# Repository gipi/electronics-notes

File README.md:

Repository containing my notes about electronics.

You can read it at [Read the docs](http://electronics-notes.readthedocs.org/).

## Getting started

You need to install the dependencies

```
$ python3 -m pip install --user mkdocs python-markdown-math
```

and to read locally you need to do a simple

```
$ mkdocs serve
```

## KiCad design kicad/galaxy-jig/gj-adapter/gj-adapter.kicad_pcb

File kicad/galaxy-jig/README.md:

# Galaxy JIG

This is a board to easily develop on Samsung's smartphones that have the serial
port activated using a particular resistor value between the ``ID`` and ``GND``
of the ``USB`` connection.

To multiplex between the two possible routes I'm using the
[ADG723](https://www.analog.com/media/en/technical-documentation/data-sheets/adg721_722_723.pdf),
a STSP switch. and the ``mode`` signal as input for the mux.

## Soldering procedure

 1. solder the ``ADG723``
 2. check they are working correctly
 3. solder the ``USB`` connector
 4. build the micro ``USB`` cable and use it to check connectivity of the connector
 5. solder the ``USB`` cable
 6. solder the ``UART`` header
 7. solder the 619k resistor

## TODO

 - **rethink the switching interface**, probably I should use the [TS3USB221](https://www.ti.com/lit/ds/symlink/ts3usb221.pdf)
 - add also a variable resistor so to change the value easily
 - move test point to the ``UART HEADER`` so to expose ``VCC`` more easily
 - add labels indicating the signal passing through the switches
 - modify footprint ``USB`` micro connector to allow easier hand soldering
 - add two leds to indicate the mode
 - use a ``FTDI`` chip to directly talk serial over ``USB``

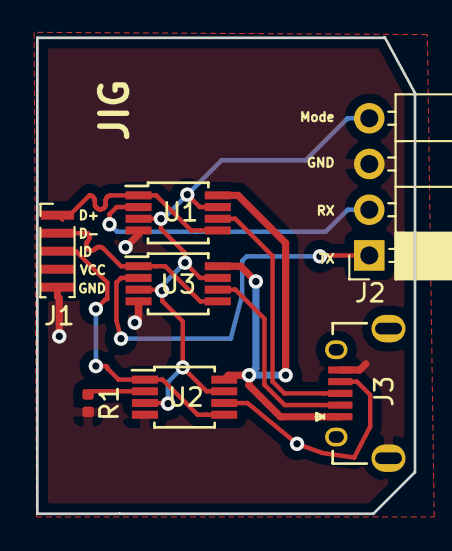
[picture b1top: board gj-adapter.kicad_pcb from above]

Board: 2 copper layers, 21.0 x 26.5 mm, 7 parts (0 on the bottom side), 12 nets.

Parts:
J1: Conn_01x05; PinHeader_1x05_P1.00mm_Vertical
J2: Conn_01x04; PinSocket_1x04_P2.54mm_Horizontal
J3: USB_B_Micro; ZX62D-B-5PA8
R1: 619k; R_0402_1005Metric
U1, U2, U3: ADG723; MSOP-8_3x3mm_P0.65mm

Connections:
D+: J1.1, U1.1, U1.5
D+-PC: J3.3, U1.6
D-: J1.2, U3.1, U3.5
D--PC: J3.2, U3.6
GND: J1.5, J2.3, J3.5, J3.6, R1.2, U1.4, U2.4, U3.4
ID-PC: J3.4, U2.6
ID-device: J1.3, U2.1, U2.5
Mode: J2.4, U1.3, U1.7, U2.3, U2.7, U3.3, U3.7
unnamed: R1.1, U2.2
RX: J2.2, U1.2
TX: J2.1, U3.2
VCC: J3.1, U1.8, U2.8, U3.8

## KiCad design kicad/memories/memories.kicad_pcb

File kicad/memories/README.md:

# Memories

Here I'm trying to create a header for the Mojo development board that allows
to have the basic minimal peripherals for a running system:

 - Flash
 - SDRAM
 - VGA
 - PS2

In this directory there are the KiCAD files and this is the hand soldered version 1.0

## Flash

The flash memory under experimentation is the NAND512W3A2C, with 512 Mbit and x8 of bus width.

 - [Datasheet](https://4donline.ihs.com/images/VipMasterIC/IC/SGST/SGSTS20436/SGSTS20436-1.pdf)

## SRAM

The SDRAM used here is the MT48LC32M8A2.

 - [Datasheet](256Mb_sdr.pdf)
 - [Tutorial](https://embeddedmicro.com/blogs/tutorials/sdram-verilog) about writing a SDRAM controller in Verilog

## VGA

It's a VGA with 3 bits for color channel using a resistor ladder.

## Todo

 - UART
 - SPI
 - I2C
 - LCD controller
 - SDCard

probably are needed only as explicit routed pinout.

## Design errors

 - The pad of the ``AMS1117`` is the ``vout`` not ground (Fixed)
 - enlarge the pad so to make it more hand-solderable
 - add mask to the Open Hardware logo (fixed)
 - reverse voltage protection
 - overvoltage protection
 - enlarge holes for VGA and PS/2 (fixed)
 - fix R-2R ladder

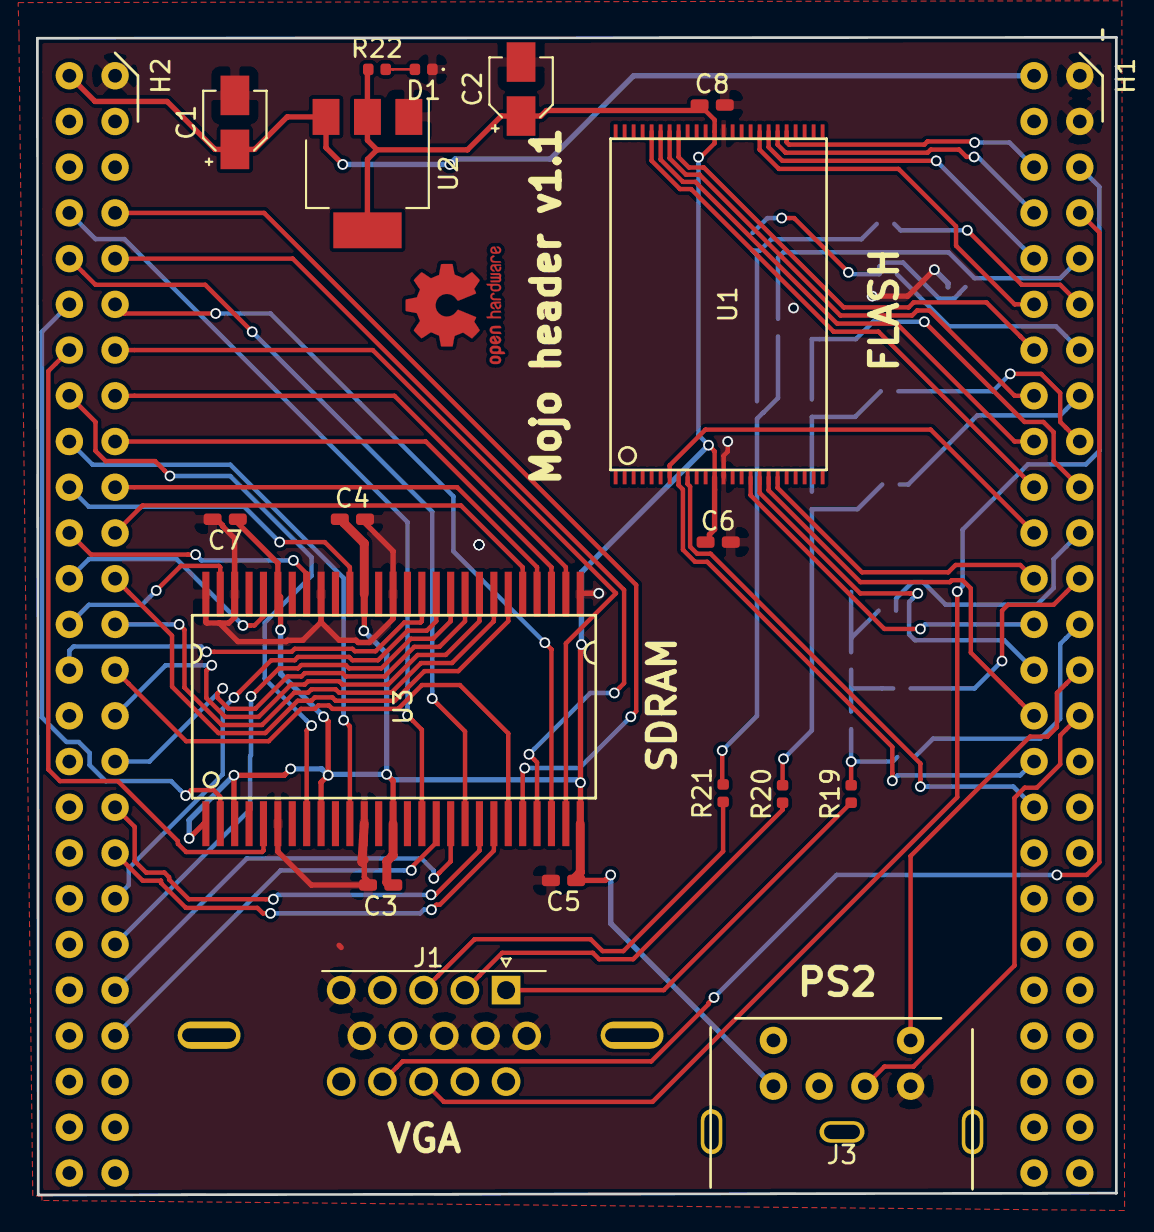
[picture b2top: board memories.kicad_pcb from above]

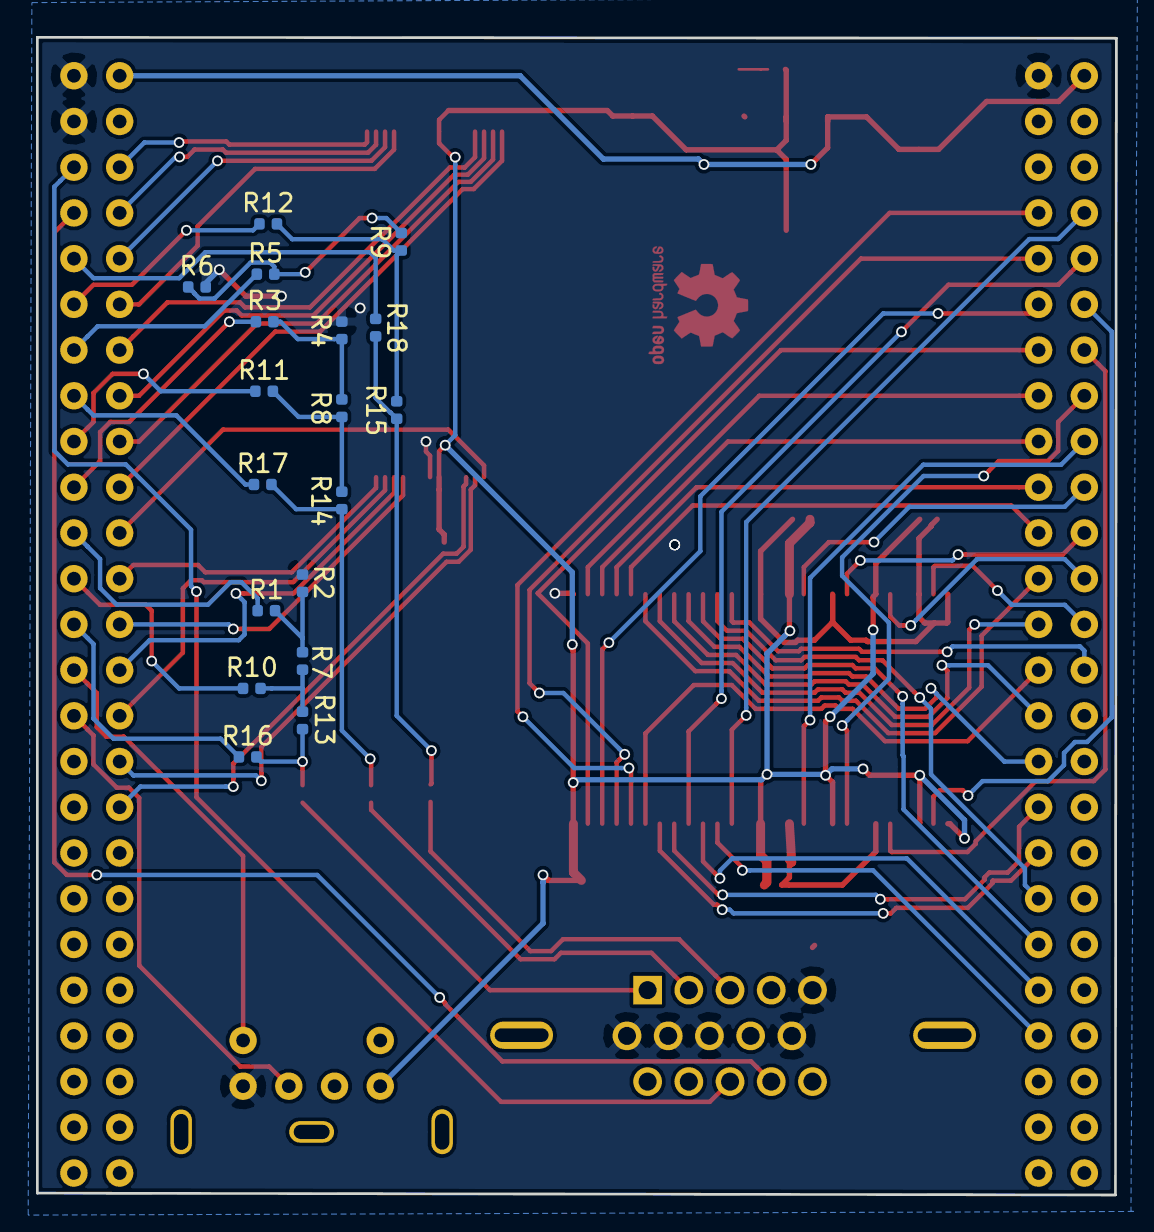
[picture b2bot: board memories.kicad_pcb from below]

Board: 2 copper layers, 59.9 x 64.3 mm, 38 parts (18 on the bottom side), 74 nets.

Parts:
C1, C2: CP1; CP_Elec_3x5.3
C3, C4, C5, C6, C7, C8: C; C_0402_handSoldering
D1: LED; LED_0402_1005Metric
H1: Header; mojo_header
H2: mojo_header_lower; mojo_header
J1: DB15_Female_HighDensity; DSUB-15-HD_Female
J3: DIN-6; mini-DIN6
R1, R2, R3, R4, R5, R6, R10, R11, R12, R16, R17, R18: 560; R_0402_1005Metric
R7, R8, R9, R13, R14, R15: 270; R_0402_1005Metric
R19, R20, R21: 0; R_0402_1005Metric
R22: R; R_0402_1005Metric
U1: NAND512
U2: AMS1117-3V3; SOT-223
U3: MT48LC32M8A2; TSOP_54

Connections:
3V3: C2.1, C3.1, C4.1, C5.1, C6.1, C7.1, C8.1, J3.4, R22.1, U1.12, U1.37, U2.2, U2.4, U3.1, U3.3, U3.9, U3.14, U3.27, U3.43, U3.49
/DQ0: H2.31, U3.2
/DQ1: H2.32, U3.5
/DQ2: H2.33, U3.8
/DQ3: H2.34, U3.11
/DQ4: H2.35, U3.44
/DQ5: H2.36, U3.47
/DQ6: H2.37, U3.50
/DQ7: H2.38, U3.53
/VGA/VGA_B0: H1.5, R18.1
/VGA/VGA_B1: H1.6, R12.1
/VGA/VGA_B2: H1.7, R5.1
/VGA/VGA_B_OUT: J1.3, R21.1
/VGA/VGA_G0: H1.8, R17.1
/VGA/VGA_G1: H1.9, R11.1
/VGA/VGA_G2: H1.10, R3.1
/VGA/VGA_G_OUT: J1.2, R20.1
/VGA/VGA_HSYNC: H1.3, J1.13
/VGA/VGA_R0: H1.13, R16.1
/VGA/VGA_R1: H1.12, R10.1
/VGA/VGA_R2: H1.11, R1.1
/VGA/VGA_R_OUT: J1.1, R19.1
/VGA/VGA_VSYNC: H1.4, J1.14
DQM: H2.39, U3.39
GND: C1.2, C2.2, C3.2, C4.2, C5.2, C6.2, C7.2, C8.2, D1.1, H1.1, H1.2, H2.1, J1.5, J1.6, J1.7, J1.8, J1.10, J3.3, R2.2, R4.2, R6.2, U1.13, U1.36, U2.1, U3.6, U3.12, U3.28, U3.41, U3.46, U3.52, U3.54
unnamed: D1.2, R22.2
unnamed: H1.28, U1.29
unnamed: H1.29, U1.30
unnamed: H1.30, U1.31
unnamed: H1.31, U1.32
unnamed: H1.32, U1.41
unnamed: H1.33, U1.42
unnamed: H1.34, U1.43
unnamed: H1.35, U1.44
unnamed: H1.36, U1.7
unnamed: H1.37, U1.19
unnamed: H1.38, U1.16
unnamed: H1.39, U1.17
unnamed: H1.40, U1.18
unnamed: H1.41, U1.8
unnamed: H1.42, U1.9
unnamed: H2.4, U3.23
unnamed: H2.5, U3.24
unnamed: H2.6, U3.25
unnamed: H2.7, U3.26
unnamed: H2.8, U3.29
unnamed: H2.9, U3.30
unnamed: H2.10, U3.31
unnamed: H2.11, U3.32
unnamed: H2.12, U3.33
unnamed: H2.13, U3.34
unnamed: H2.14, U3.22
unnamed: H2.15, U3.35
unnamed: H2.16, U3.36
unnamed: H2.17, U3.20
unnamed: H2.18, U3.21
unnamed: H2.19, U3.38
unnamed: H2.20, U3.37
unnamed: H2.21, U3.18
unnamed: H2.22, U3.17
unnamed: H2.29, U3.16
unnamed: H2.30, U3.19
unnamed: R1.2, R2.1, R7.2
unnamed: R3.2, R4.1, R8.2
unnamed: R5.2, R6.1, R9.2
unnamed: R7.1, R10.2, R13.2
unnamed: R8.1, R11.2, R14.2
unnamed: R9.1, R12.2, R15.2
unnamed: R13.1, R16.2, R19.2
unnamed: R14.1, R17.2, R20.2
unnamed: R15.1, R18.2, R21.2
PS2_CLK: H1.14, J3.5
PS2_DATA: H1.15, J3.1
V_EXTERNAL: C1.1, H1.26, H2.26, U2.3

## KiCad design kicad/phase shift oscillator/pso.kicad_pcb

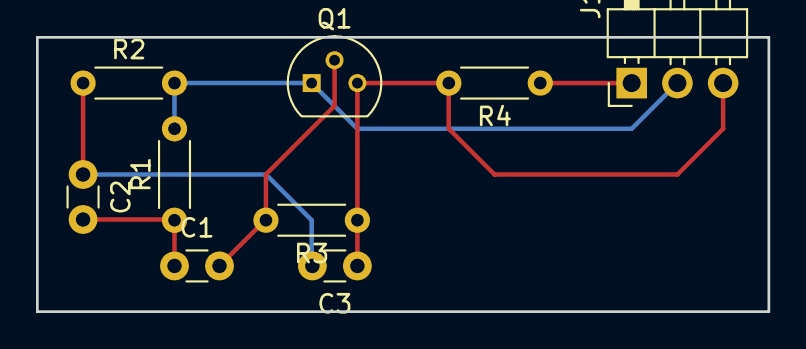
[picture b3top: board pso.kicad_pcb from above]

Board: 2 copper layers, 40.6 x 15.2 mm, 9 parts (0 on the bottom side), 6 nets.

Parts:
C1, C2, C3: 10nF; C_Disc_D3.0mm_W1.6mm_P2.50mm
J1: Conn_01x03; Pin_Header_Angled_1x03_Pitch2.54mm
Q1: 2N3904; TO-92_Molded_Narrow
R1, R2, R4: 2.2k; R_Axial_DIN0204_L3.6mm_D1.6mm_P5.08mm_Horizontal
R3: 220k; R_Axial_DIN0204_L3.6mm_D1.6mm_P5.08mm_Horizontal

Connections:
GND: J1.2, Q1.1, R1.2, R2.2
unnamed: C1.1, C2.2, R1.1
unnamed: C1.2, Q1.2, R3.2
unnamed: C2.1, C3.2, R2.1
VCC: J1.1, R4.1
Vout: C3.1, J1.3, Q1.3, R3.1, R4.2

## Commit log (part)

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2016-10-25 Add piece of code.
2016-10-26 fpga: counter increase with button pressing.
2016-12-02 Add links.
2016-12-13 Add note.
2016-12-30 Add Kicad links.
2017-01-10 Improve logic level notes.
2017-02-05 Improve KiCAD.
2017-02-05 Add an EasyDriver example sketch.
2017-02-12 Add opamp section.
2017-02-12 Add TODO.
2017-02-18 Add section about tape.
2017-02-18 Add note about enameled wire.
2017-02-20 Add 3D section.
2017-02-27 Add note about FDM.
2017-03-08 Add video.
2017-03-26 Try to use coregen.
2017-04-23 kicad: add simple audio amplifier circuit.
2017-05-08 Add Atmel's datasheets section.
2017-05-08 Add note about datasheet related infos.
2017-05-08 Fix link.
2017-05-15 Add example for setting fuse with avrdude.
2017-05-16 fpga: first module to dirty-glitching.
2017-05-19 fpga: very dirty code to glitch a clock.
2017-05-29 Fix.
2017-06-06 avr: add ISP pinout.
2017-06-06 laws: add note.
2017-06-06 RN42: improve info about default conf connection.
2017-06-07 RN42: add link to firmware stuff.
2017-06-30 RN42: update BOM.
2017-08-09 add SMA connectors information.
2017-12-06 VGA: add schematics.
2017-12-06 Add AVR444 application note code ported to avr-gcc.
2017-12-10 Add phase oscillator with kicad.
2017-12-10 Add page about simulation with spice.
2017-12-16 Dump some links.
2018-01-10 fpga: add PS2 simple controller.
    No error detection!
2018-01-10 fpga: add shift register verilog implementation.
2018-01-11 fpga/VGAGlyph: big rework.
2018-01-12 fpga/VGA: fix constraints file.
2018-01-12 fpga/VGAGlyph: fix reversed glyphs ROM and glyph_address.
2018-01-13 fpga/VGAGLyph: fix font rendering.
2018-01-13 fpga/VGAGlyph: add testbench for the framebuffer module.
    This testbench is probably bad written.
2018-02-19 Add script to read data from the SIGLENT SDS1102CML oscilloscope.
2018-02-20 test_visa: close device once.
2018-02-20 test_visa: display IDN for all the command involving the opened device.
2018-02-20 test_visa: add dumpscreen command.
2018-02-20 test_visa: add waveform dumping command.
2018-03-17 fpga: project GlitchGen.
2018-03-22 fpga/mojo/GlitchGen: add Arduino sketch.
2018-03-22 fpga/mojo/GlitchGen: refactor module for clock generation.
2018-04-11 GlitchGen: single stepping OK!
2018-04-11 GlitchGen: fix typo.
2018-04-11 GlitchGen: remove internal useless signal.
2018-04-11 GlitchGen: put the mojo clock into the clock network.
    In this way we can use it as a clock in the following modules.
2018-04-11 GlitchGen: make leds indicate some useful state.
2018-05-07 ESC: add simple code to use an ESC with arduino.
2018-05-10 PS/2: add working code.
2018-06-14 VGAGlyph: fix synch issue (?).
2018-06-14 VGAGlyph: use the same clock for h/vsync and framebuffer.
2018-06-14 Add reset input to VGA module.
2018-06-16 Change default net type to none.
2018-06-16 Let inDisplayArea be in sync with CounterX and CounterY.
2018-06-16 Delay also inDisplayArea.
2018-06-16 Improve comment.
2018-07-16 kicad: add mojo shield.
    It contains SDRAM, Flash, VGA and PS2.
2018-08-19 Fix AMS1117 pad net.
    In the original datasheet is not indicated that the bigger pad is vout
    and not ground how any sensible human could think.
2018-08-27 Fix the read the docs configuration file.
2018-09-08 fpga: fix UCF for SDRAM.
2018-09-08 fpga: rename variable.
2018-09-08 kicad: improve info about memories board.
2018-09-12 kicad: mojo header PS/2 holes enlargement.
2018-09-13 kicad: enlarged footprint for capacitor 0402 for hand soldering.
2018-09-24 kicad: fix name for mojo header pins.
2018-09-24 kicad/memories/pcb: fix R-2R ladder labels.
2018-10-03 fpga/VGA: upgrade controller to use 9-bit color depth.
2018-12-04 AVR/KeyboardMatrixRecovery: add POC.
2018-12-07 KeyboardMatrixRecovery: improve matrix recovery sketch.
    Now print only a key the moment when is pressed and output a binary packet.
2018-12-08 RN42: add datasheet.
2018-12-09 AVR/KeyboardMatrixRecovery: update README.
2018-12-28 Fix markdown extension error.
    <Config value: 'markdown_extensions'. Error: Failed to initiate extension 'math': 'module' object has no attribute 'makeExtension'>
    probably the naming convention is changed and had to be fixed, see
    <https://python-markdown.github.io/change_log/release-2.5/>.
2019-02-03 VGASOC: add ring_counter module and verilator POC.
2019-03-31 kicad: add samsung-jig.
2019-03-31 kicad: semi-final version of galaxy-jig.
2019-04-07 Add diagram of the JTAG stack.
2019-04-07 Fix typo.
2019-05-19 kicad/galaxy-jig: add notes.
2020-05-12 fpga/VGAGlyph: implement block ram and its simulation.
2020-05-12 fgpa/VGAGlyph: reimplement block rom for the glyph with simulation.
    Launch sim/obj_dir/Vglyph_rom and see the output of the block rom.
2020-05-12 fpga: add reset signal to hvsync_generator.
2020-05-12 fpga/VGAGlyph: rework verilog so to have simulation.
    $ cd fpga/mojo/VGAGlyph/sim
    $ make vga && ./obj_dir/VVGA
    ...
    [+] starting VGA simulation
    [-> dumping frame frames/frame-00000000.bmp at idx 6]
    [-> dumping frame frames/frame-00000001.bmp at idx 1182312]
2020-05-14 fpga/VGASOC: start implementing CPU.
2020-05-17 fpga/VGASOC: first implementation of the load instruction assembly.
2020-05-17 Add some links and notes.
2020-05-17 fpga/VGAGlyph: add clean target.
2020-05-17 fpga/VGASOC: add note about flags.
2020-05-17 fpga/VGASOC: fix compilation warning.
2020-05-18 fpga/VGASOC: remove MOVE instruction.
    Can be implemented with "ld rd, rs".
2020-05-21 fpga/VGASOC: factorize code about pipeline and add tests.
2020-05-21 Fix bug on parsing left operand.
2020-05-21 fpga/VGASOC: rework a little LOAD instruction assembly.
2020-05-21 fpga/VGASOC: start to implement JUMP instruction.
2020-05-23 fpga/VGASOC: improve Instruction{,Impl} classes.
2020-05-23 fpga/VGASOC: improve jump instruction.
    Now save the return address.
2020-05-23 fpga/VGASOC: start implementing the flags register.
2020-05-23 fpga/VGASOC: start implementing add instruction.
2020-05-23 fpga/VGASOC: improve operand parsing.
2020-05-23 Cleaning.
2020-05-26 fpga/VGASOC: add fetch module.
2020-05-26 Ignore obj_dir/
2020-05-27 fpga/VGASOC: improve fetch module.
2020-05-31 fpga/VGASOC: reworking decode and execute modules.
2020-05-31 fgpga/VGASOC: give a default (void) implementation for validate() and parseOpcode().
2020-06-02 fpga/VGASOC: start to organize the internal memory.
2020-06-02 fpga/VGASOC: change bootrom code (now with relative jumps!).
2020-06-02 fpga/VGASOC: implement relative jump.
2020-06-02 fpga/VGASOC: improve assembler output.
2020-06-02 fpga/VGASOC: bootrom -> wb_memory.
    Change the name to reflect the generic use.
2020-06-03 fpga/VGASOC: implement multiplication.
2020-06-03 fpga/VGASOC: use some parameters.
2020-06-03 fpga/VGASOC: set next program counter at the decode phase.
    So we don't have a race condition with the jump instruction.
2020-06-03 fpga/VGASOC: improve boolean condition.
2020-06-06 fpga/SOC: rename project.
2020-06-06 fpga/SOC: start to implement the memory stage.
2020-06-06 fpga/SOC: start implementing push instruction.
    Now we are writing to memory, we modified the fetch module as a general
    purpose master wishbone controller (a lot remains to do to have something
    not so shitty).
2020-06-06 fpga/SOC: rework enable_fetch.
    The enable signal for the wishbone master must be "one-shot", I'm not sure
    how good this strategy is.
2020-06-06 fpga/SOC: hardfix the simulation logging.
2020-06-06 fpga/SOC: add comments and .word directive.
2020-06-07 fpga/SOC: fix(?) write enable signal for the fetch module.
2020-06-07 fpga/SOC: add subroutine to the bootrom.
2020-06-08 fpga/SOC: start implementing pop instruction.
    FIXME: the input line for the memory is not driven so the push itself
    is not working.
2020-06-08 fpga/SOC: handle empty lines in the assembler.
2020-06-14 fpga/SOC: rework assembler to handle labels.
    Logging added with plog.
2020-06-14 fpga/SOC: fix internal SRAM size.
2020-06-14 fpga/SOC: update README.
2020-06-20 fpga/SOC: refactor code:
    Separate ISA from simulation and create distinct Makefiles.
2020-06-20 fpga/SOC: fix i_addr signal width.
2020-06-21 fpga/SOC: use stderr for logging.
2020-06-21 fpga/SOC: refactor bootrom code into its own directory.
2020-06-21 fpga/SOC: improve ISA documentation with opcode list.
2020-06-21 fpga/SOC: improve "unit testing" for instructions.
2020-06-21 fpga/SOC: fix directive encoding.
2020-06-24 fpga/SOC: fix jump instruction test.
2020-06-24 fpga/SOC: use the actual address contained in PC, not the incremented one.
2020-06-24 fpga/ROM: remove code I don't remember anymore.
2020-07-05 fpga/SOC: a little rework of Makefiles.
2020-07-05 fpga/SOC: use localparam.
2020-07-05 fpga/SOC: de-assert o_done when starting transmissions.
2020-07-05 fpga/SOC: add primitive wishbone controller for UART.
2020-07-06 fpga/SOC: improve and add test for wb_uart.
2020-07-12 fpga/SOC: rework flags handling.
2020-07-12 fpga/SOC: rework cpusim to use SysCon class.
2020-07-12 fpga/SOC: handle memory transaction during instructions tests.
2020-07-12 fpga/SOC: import gtkwave predefined signals "save file".
2020-07-13 fpga/SOC: don't use hex for registers index.
2020-07-13 fpga/SOC: add tests for pop/push instructions.
2020-07-14 fpga/SOC: implement store instruction.
2020-07-14 fpga/SOC: add check for wishbone write enable signal during tests.
2020-07-18 fpga/SOC: port soc.cpp to use peripherals templates.
2020-07-18 Fix uart
2020-07-18 Improve README.
2020-07-19 fpga/SOC: add baudgenerator module.
    For now is only simulated with clk generated equals to the main one.
2020-07-19 fpga/SOC: rework memory accesses to allow variable sizes.
    Now it's possible to have byte/short/word sized accesses.
2020-07-19 fpga/SOC: start to implement variable encoding assembler output.
2020-07-19 fpga/SOC: save gtkwave signal configuration for the SoC.
2020-07-26 fpga/SOC: remove traces when cleaning.
2020-07-26 fpga/SOC: make the bootrom path absolute.
2020-08-08 Fix counter wrong size.
    Thank to @MuhammadAlBarham for spotting the error. This fixes #1 .
2020-12-17 fpga/SOC/asm: add check for the right operand of a LD instruction.
2020-12-17 fpga/SOC: improve simulation for glyph ROM.
2020-12-17 fpga/SOC: add new test case.
2020-12-17 fpga/SOC: add header file dependencies for asm.
2020-12-17 fpga/SOC: add note about 4 bytes aligning for PC and SP.
2020-12-17 fpga/SOC: rework wishbone bus.
2020-12-18 fpga/SOC: make ACK for slave HiZ when not selected.
2020-12-18 fpga/SOC: rework tick().
2020-12-18 fpga/SOC: use enum for opcodes.
2020-12-18 fpga/SOC: fix slave selection logic.
2020-12-18 fpga/SOC: add jump relative test.
2020-12-18 fpga/SOC: improve logging on cpu simulation.
    Add description of the specific tests.
2021-03-24 Add note about solder wick.
2021-03-24 Update pinout image.
2021-04-17 Add requirements file.
2021-04-17 Fix image path.
2021-04-17 Add readthedocs configuration file.
2021-04-17 Add Arduino Mega pinout.
2021-04-22 Fix AVR makefile.
2021-04-22 Add code for ecg.
2021-04-22 AVR/ECG: reformat code for USB_COM_vect.
2021-04-22 AVR/ECG: fix wrong register for DETACH.
2021-04-22 AVR/ECG: add ADC routines.
2021-04-23 AVR/ECG: configure for the AD8232 board.
2021-04-23 AVR/ECG: fix declaration.
2021-04-23 AVR/sd-reader: import project from www.roland-riegel.de/sd-reader/.
2021-04-23 AVR/SD-READER: adapt code for atmega32u4.
2021-04-25 AVR/blink: add simple project to blink a led.
2021-04-29 STM32: add PoC blink baremetal.
2021-05-04 Fix SD Card related links.
2021-06-18 Fix micro pinout.
2021-06-24 AVR/KeyboardMatrixRecovery: add script to generate layout.
2021-10-20 Add some links.
2021-11-27 Add note about leds orientation.
2021-11-27 Add note about capacitor applications.
2021-12-05 Update mkdocs version.
2022-04-03 Add some notes
2022-04-03 Update dependencies.
